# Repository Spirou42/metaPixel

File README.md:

# metaPixel
**A colourful open source art project.**

![Plasma Image][plasmaStripes]

## Description
metaPixel is a (mostly) 3D printed, modular, extendable, magnetic pixel display for showing "retro" animations well known from the *good old days*™.

![metaPixel Design][metaPixelAll]
The whole design uses a lot of magnets for adding strength to inter module connections, to hold the module cover and diffusors in place or to stick the modules onto the steel base.

The metaPixel display consists of 4 main parts:

1. steel plate
2. 20 metaPixel modules
3. controller and power supply 
4. Frame with connectors 

### Steel plate
The central structure of the whole installation is a 700 x 700 x 0.5 mm sheet of black painted steel. Both, the display modules as well as the controller and the power supply are attached with magnets to both sides of the plate.

### Frame
The steel plate is mounted to a wood frame with 20 ring magnets. 
![Frame][metaPixelFrame]

The wood frame contains cut outs for a standard power connector as well as for DMX (3 pin XLR) and USB connectors. 
![CutOuts][metaPixelFrameCutOuts]

### metaPixel Module
Each module contain 20 "intelligent" RGB LEDs in a 4 by 5 grid on a small printed carrier board.
![LED Stripes][ledStripes] 

The modules interconnect via a 3 pin connector. While the power connections goes straight from the input to the output with taps for each LED stripe. The data signal is routed on a zigzag path trough the stripes.
![metaPixel Box][metaPixelBox]

The LED carrier rests on top of four pillars which also contain some of the magnets.
![metaPixel Box with LEDs][metaPixelLedBox]

Four magnets in the corners of the box holds the cover and grid in place.
![metaPixelWholeBox][metaPixelWholeBox]

[plasmaStripes]: Resources/Color_lines.jpg "Plasma Stripes"
[ledStripes]: Resources/LEDs.png "LED-Base"
[metaPixelBox]: Resources/Box.png "megaPixel box with connectors"
[metaPixelLedBox]: Resources/LED_BOX.png "box with LED carrier"
[metaPixelFrame]: Resources/Frame.png "Frame with connectors and magnets"
[metaPixelFrameCutOuts]: Resources/FrameCutouts.png "Frame connectors"
[metaPixelAll]: Resources/metaPixelFull.png "metaPixel Display"
[metaPixelWholeBox]: Resources/metaPixel-Full.png "a full rendered metaPixel module"
[allParts]: Resources/Components.jpg "Photo of all parts of a metaPixel"

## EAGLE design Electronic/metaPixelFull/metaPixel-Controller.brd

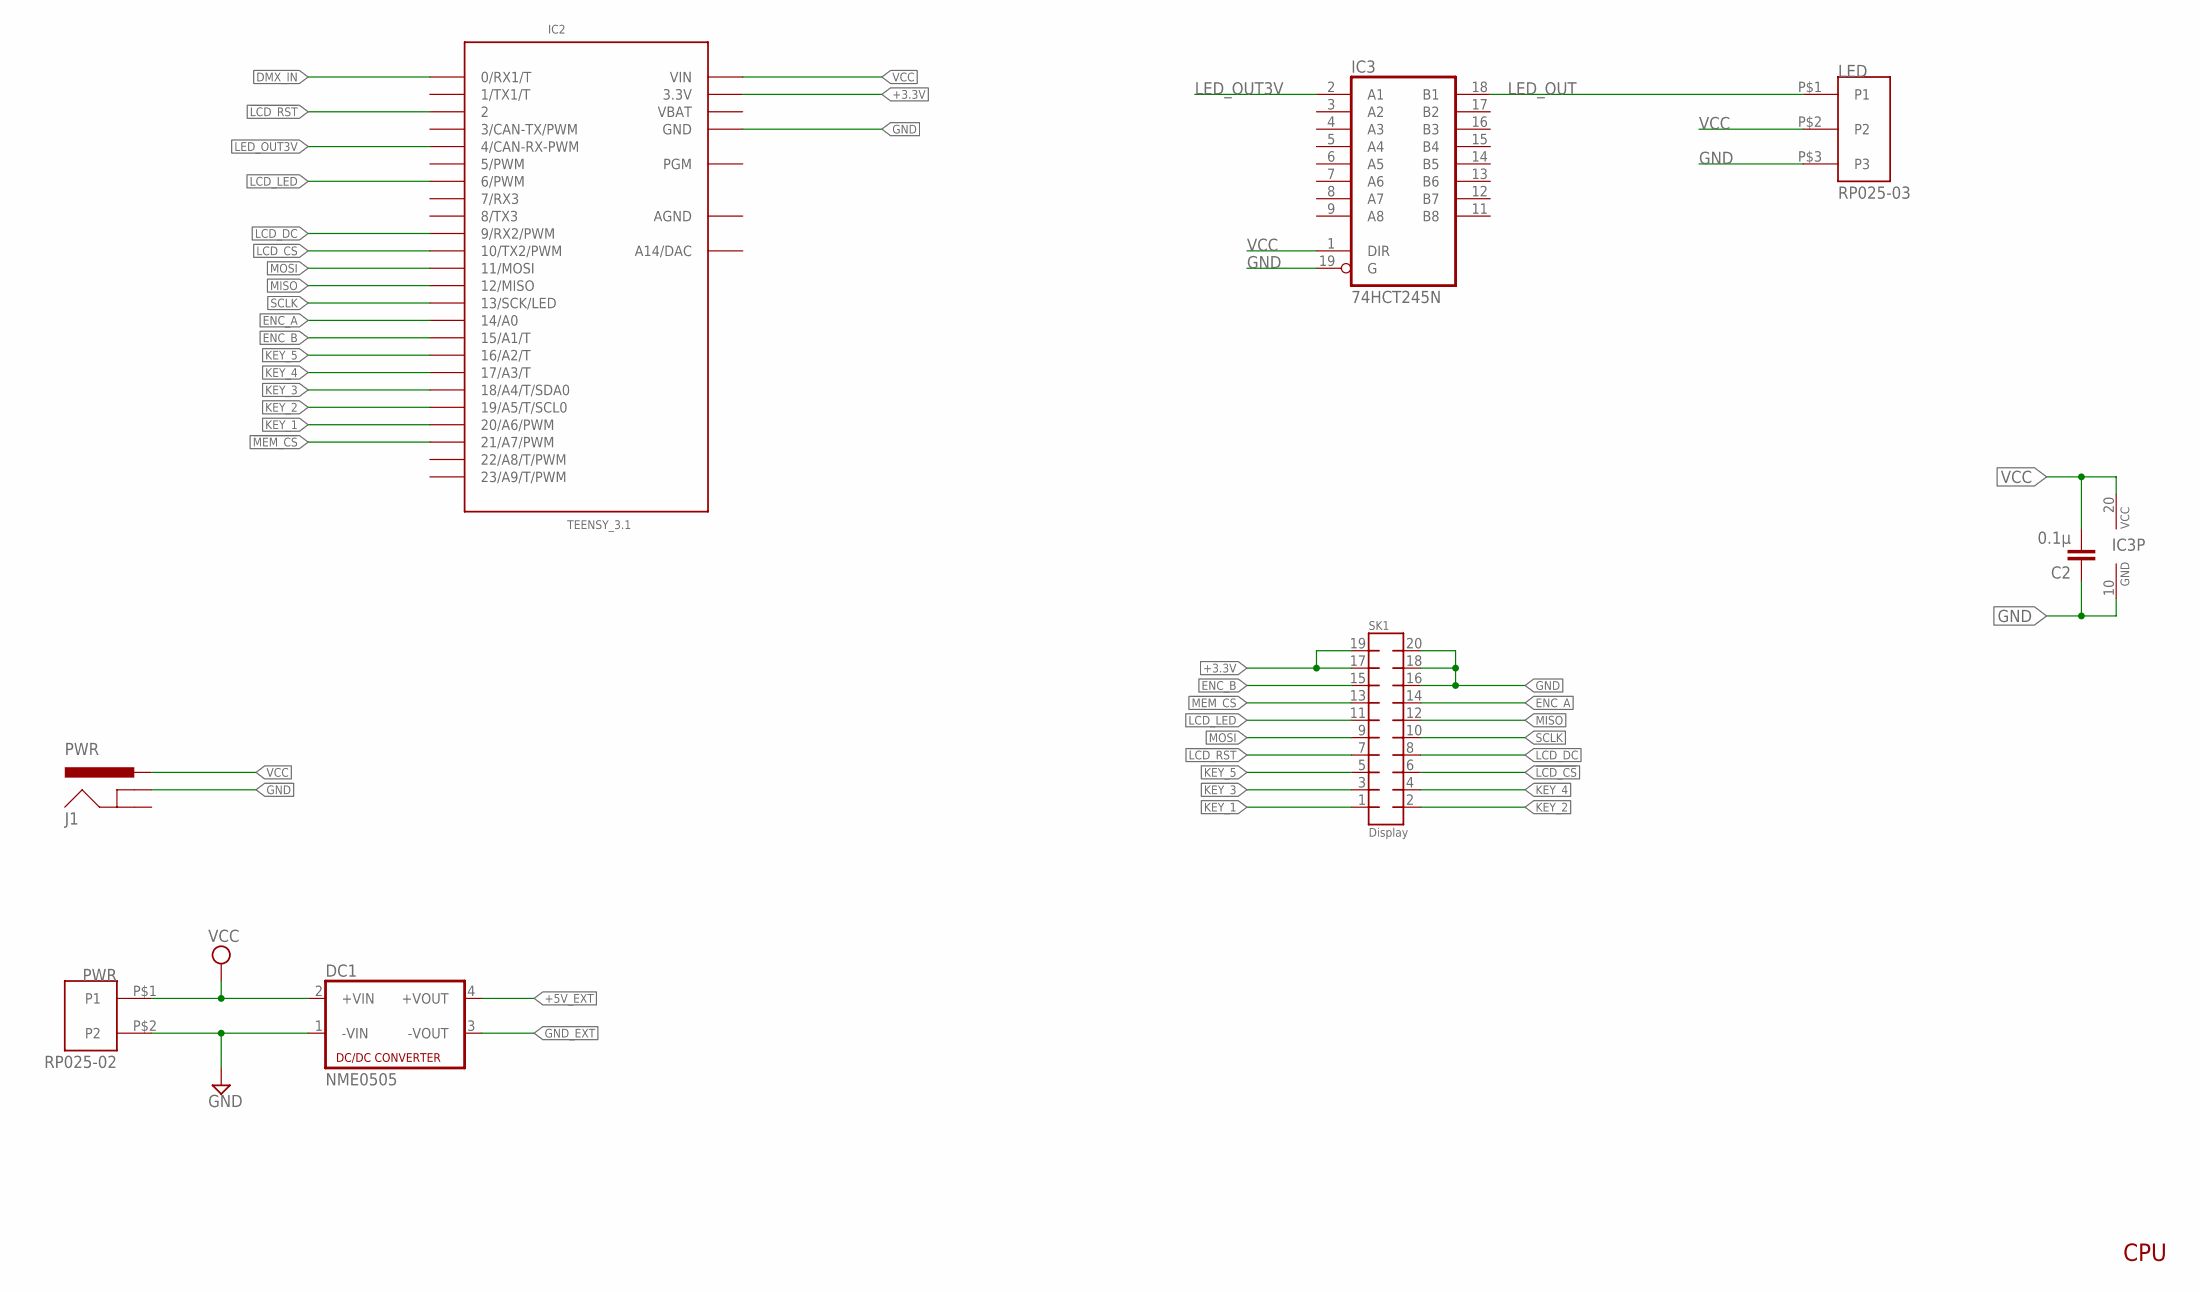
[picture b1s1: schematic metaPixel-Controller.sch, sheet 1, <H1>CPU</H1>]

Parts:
C2: 0.1µ; C025-030X050
DC1: NME0505; NME
IC2: TEENSY_3.1; TEENSY3-OUTER_ROW
IC3: 74HCT245N; DIL20
J1: PWR; POWER_JACK_SLOT
LED: RP025-03
PWR: RP025-02
SK1: Display; AMP-215079-20

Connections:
!LCD_CS: IC2.10 (10/TX2/PWM), SK1.6
!LCD_RST: IC2.2, SK1.7
!MEM_CS: IC2.21/A7 (21/A7/PWM), SK1.13
+3.3V: IC2.3.3V, IC2.3.3V1 (3.3V), SK1.17, SK1.19
+5V_EXT: DC1.4 (+VOUT); also elsewhere on the board
AGND: IC2.AGND
DMX_IN: IC2.0 (0/RX1/T); also elsewhere on the board
ENC_A: IC2.14/A0, SK1.14
ENC_B: IC2.15/A1 (15/A1/T), SK1.15
GND: C2.1, DC1.1 (-VIN), IC2.GND, IC2.GND1 (GND), IC3.10 (GND), IC3.19 (G), J1.GND@1 (GNDBREAK), LED.P$3 (P3), PWR.P$2 (P2), SK1.16, SK1.18, SK1.20; also elsewhere on the board
GND_EXT: DC1.3 (-VOUT); also elsewhere on the board
KEY_1: IC2.20/A6 (20/A6/PWM), SK1.1
KEY_2: IC2.19/A5 (19/A5/T/SCL0), SK1.2
KEY_3: IC2.18/A4 (18/A4/T/SDA0), SK1.3
KEY_4: IC2.17/A3 (17/A3/T), SK1.4
KEY_5: IC2.16/A2 (16/A2/T), SK1.5
LCD_DC: IC2.9 (9/RX2/PWM), SK1.8
LCD_LED: IC2.6 (6/PWM), SK1.11
LED_OUT: IC3.18 (B1), LED.P$1 (P1)
LED_OUT3V: IC2.4 (4/CAN-RX-PWM), IC3.2 (A1)
MISO: IC2.12 (12/MISO), SK1.12
MOSI: IC2.11 (11/MOSI), SK1.9
SCLK: IC2.13 (13/SCK/LED), SK1.10
VBAT: IC2.VBAT
VCC: C2.2, DC1.2 (+VIN), IC2.VIN, IC3.1 (DIR), IC3.20 (VCC), J1.PWR, LED.P$2 (P2), PWR.P$1 (P1); also elsewhere on the board

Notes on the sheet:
CPU

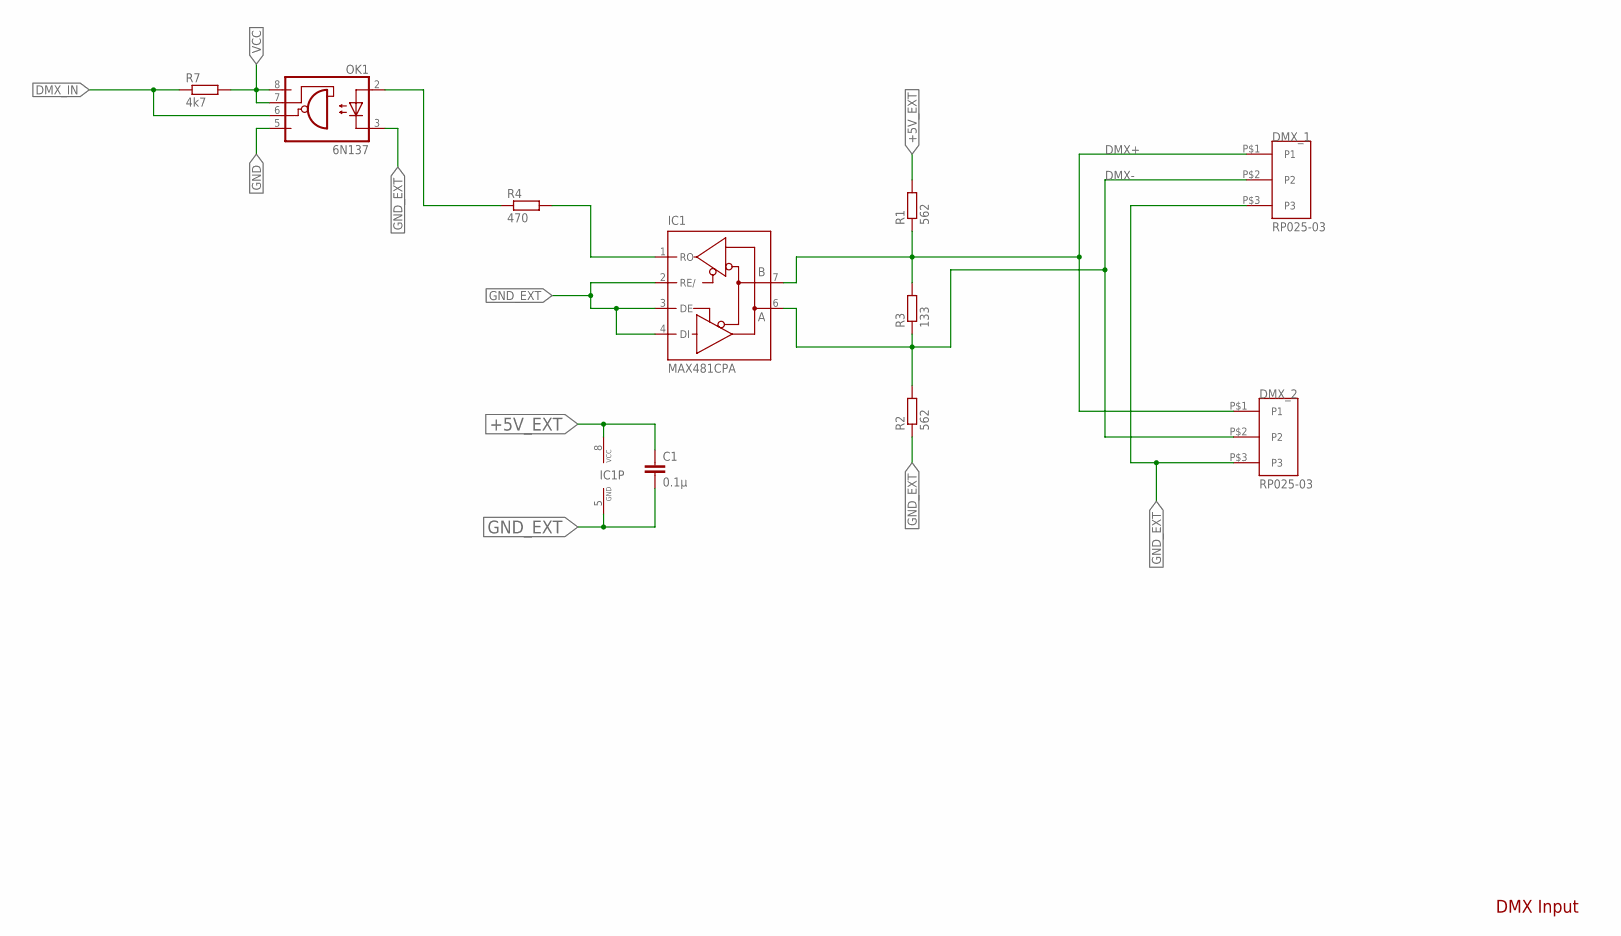
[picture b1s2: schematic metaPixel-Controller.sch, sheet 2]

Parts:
C1: 0.1µ; C025-030X050
DMX_1, DMX_2: RP025-03
IC1: MAX481CPA; DIL08
OK1: 6N137; DIL08
R1, R2: 562; 0207/7
R3: 133; 0207/7
R4: 470; 0207/10
R7: 4k7; 0207/10

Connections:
+5V_EXT: C1.1, IC1.8 (VCC), R1.2; also elsewhere on the board
DMX+: DMX_1.P$1 (P1), DMX_2.P$1 (P1), IC1.7 (B), R1.1, R3.2
DMX-: DMX_1.P$2 (P2), DMX_2.P$2 (P2), IC1.6 (A), R2.2, R3.1
DMX_IN: OK1.6 (VO), R7.1; also elsewhere on the board
GND: OK1.5 (GND); also elsewhere on the board
GND_EXT: C1.2, DMX_1.P$3 (P3), DMX_2.P$3 (P3), IC1.2 (RE/), IC1.3 (DE), IC1.4 (DI), IC1.5 (GND), OK1.3 (C), R2.1; also elsewhere on the board
unnamed: OK1.2 (A), R4.1
unnamed: IC1.1 (RO), R4.2
VCC: OK1.7 (VE), OK1.8 (VCC), R7.2; also elsewhere on the board

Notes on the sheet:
DMX Input

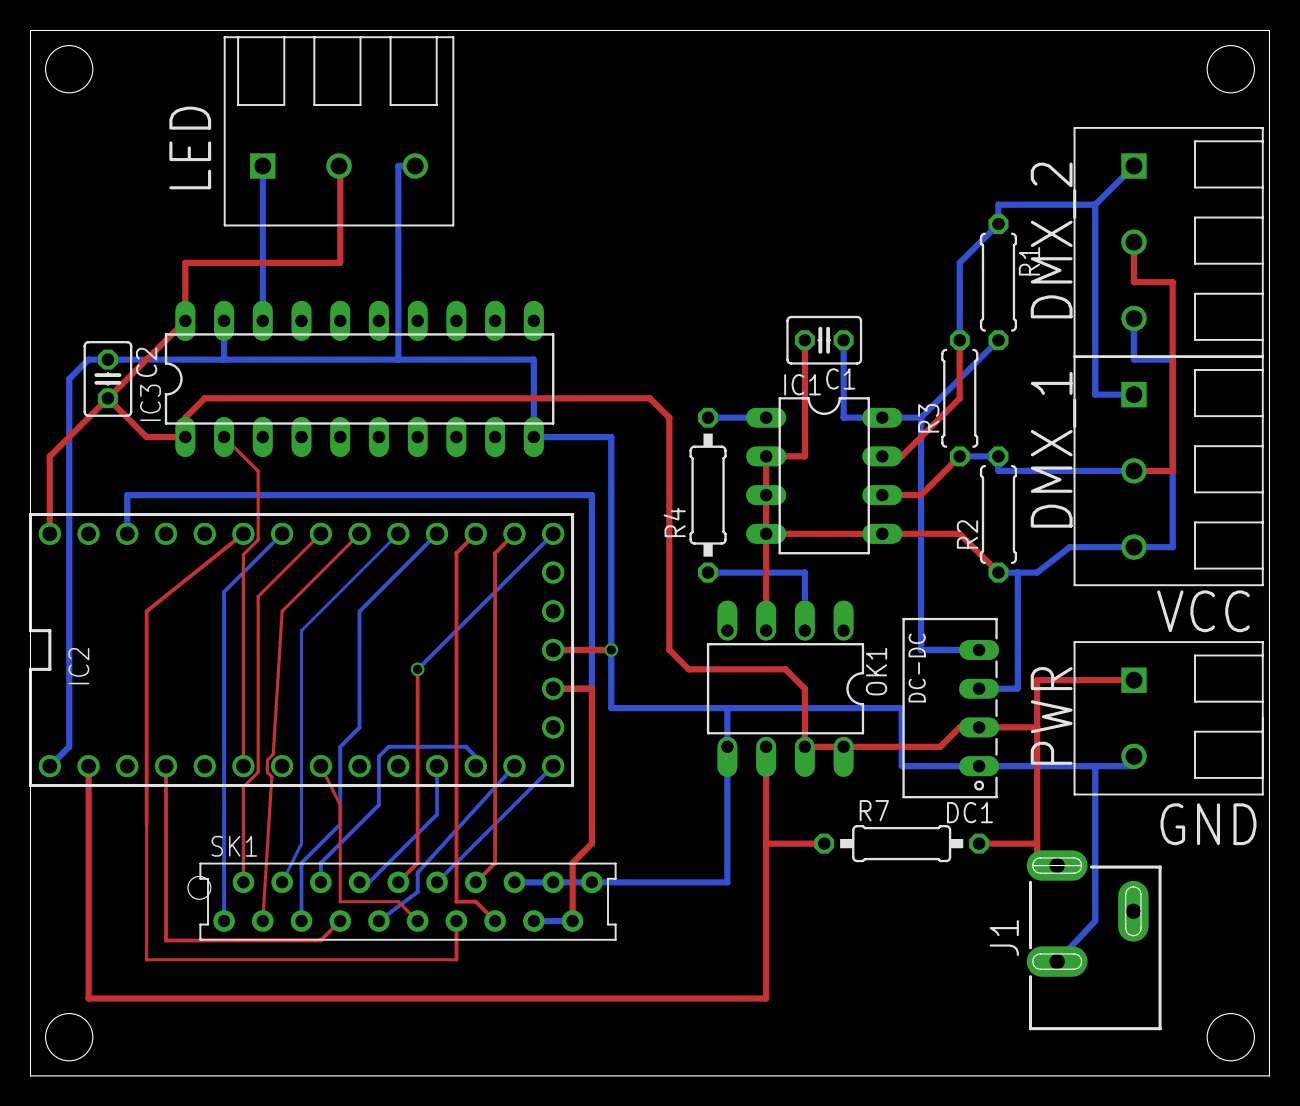
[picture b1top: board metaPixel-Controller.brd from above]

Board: 2 copper layers, 81.3 x 68.6 mm, 18 parts (0 on the bottom side), 27 nets.

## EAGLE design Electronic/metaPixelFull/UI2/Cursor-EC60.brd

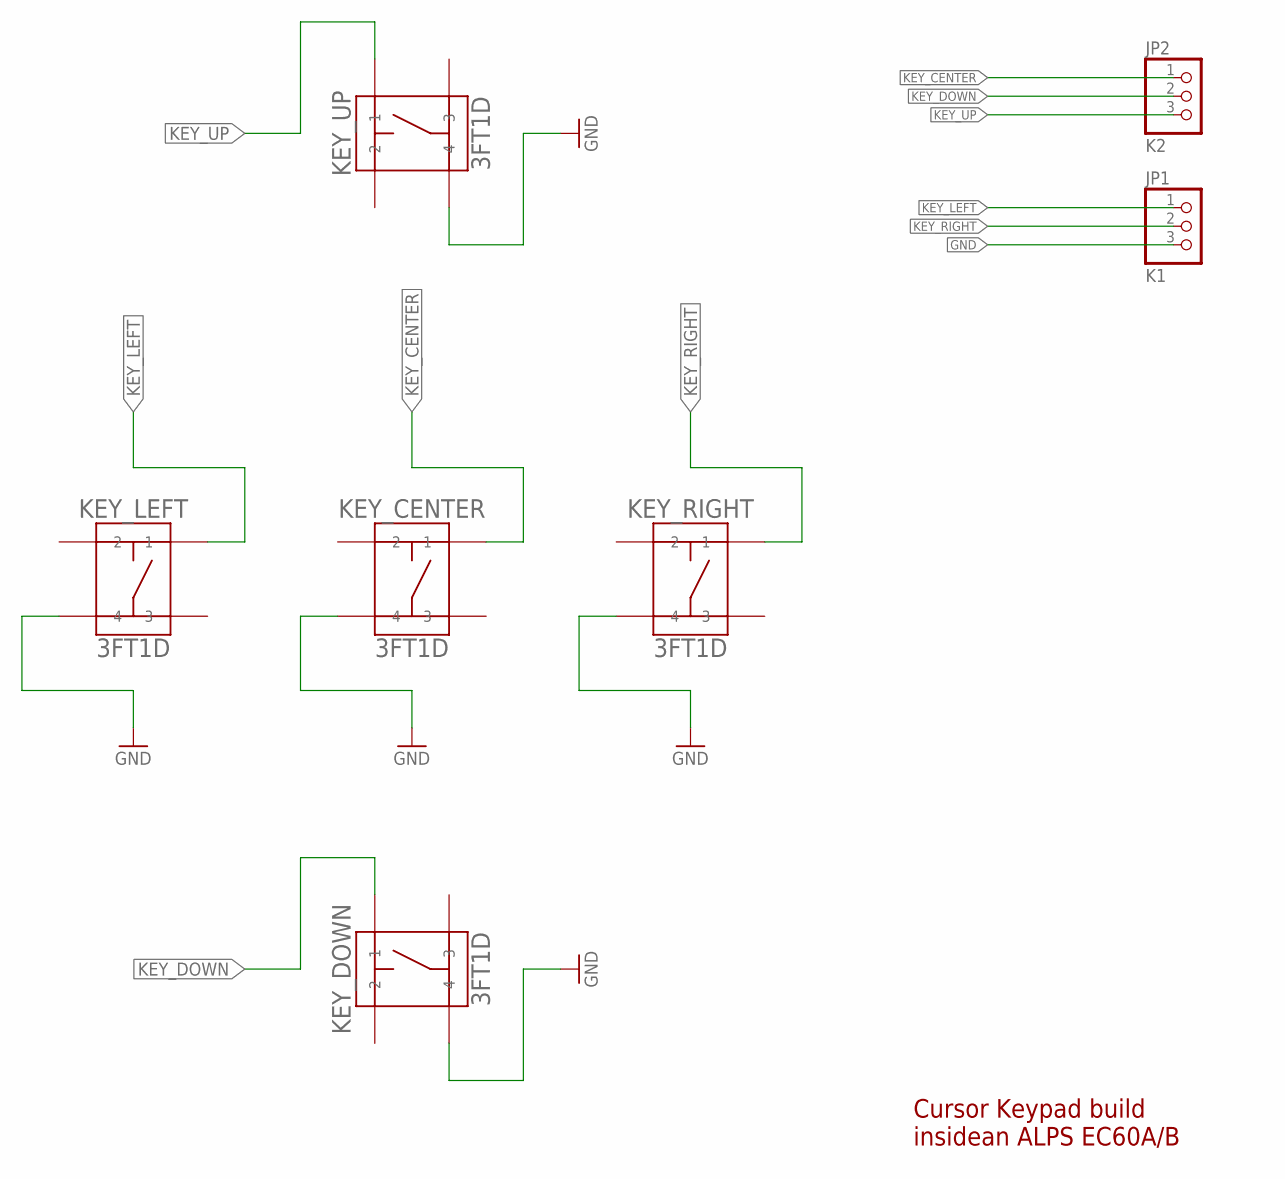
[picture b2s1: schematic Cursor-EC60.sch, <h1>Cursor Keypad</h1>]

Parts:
JP1: K1; 1X03
JP2: K2; 1X03
KEY_CENTER: 3FT1D; 3FT
KEY_DOWN: 3FT1D; 3FT
KEY_LEFT: 3FT1D; 3FT
KEY_RIGHT: 3FT1D; 3FT
KEY_UP: 3FT1D; 3FT

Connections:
GND: JP1.3, KEY_CENTER.P$4 (4), KEY_DOWN.P$4 (4), KEY_LEFT.P$4 (4), KEY_RIGHT.P$4 (4), KEY_UP.P$4 (4)
KEY_CENTER: JP2.1, KEY_CENTER.P$1 (1)
KEY_DOWN: JP2.2, KEY_DOWN.P$1 (1)
KEY_LEFT: JP1.1, KEY_LEFT.P$1 (1)
KEY_RIGHT: JP1.2, KEY_RIGHT.P$1 (1)
KEY_UP: JP2.3, KEY_UP.P$1 (1)

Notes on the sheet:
Cursor Keypad build insidean ALPS EC60A/B

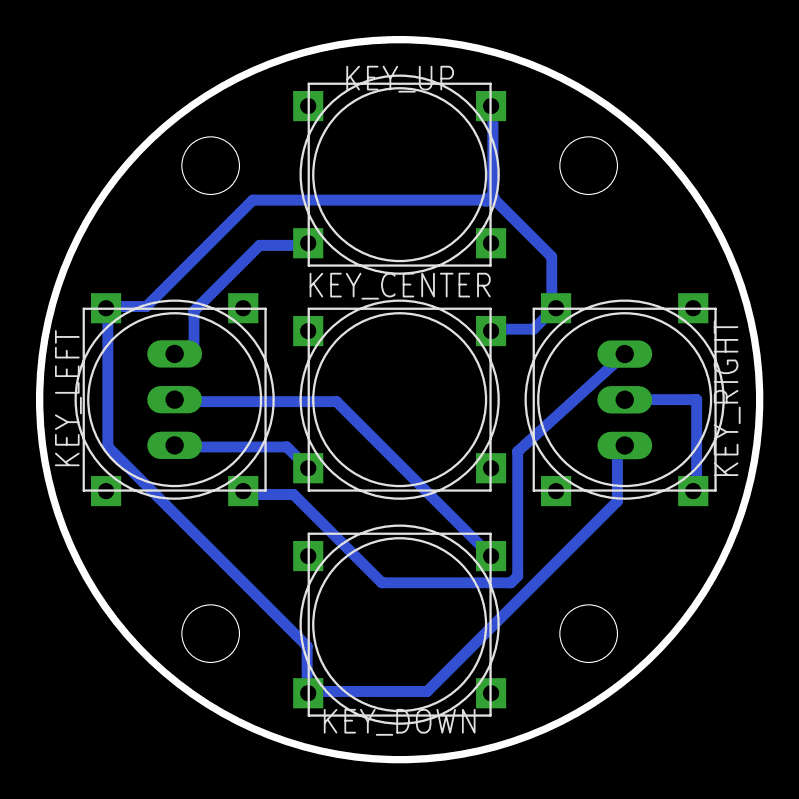
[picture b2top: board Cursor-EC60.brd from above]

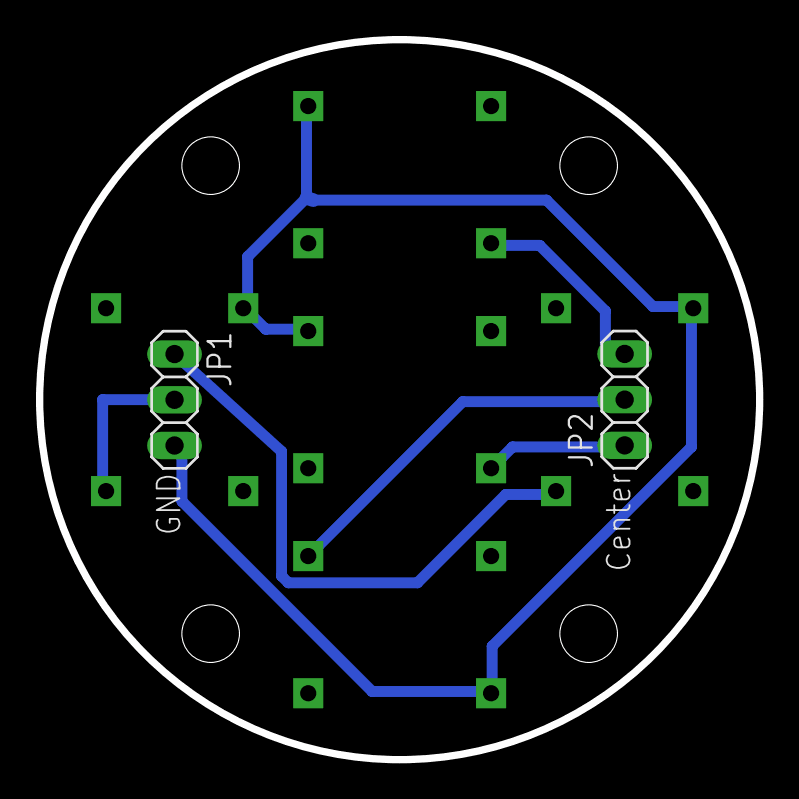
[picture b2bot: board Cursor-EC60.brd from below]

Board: 2 copper layers, 40.0 x 40.0 mm, 7 parts (2 on the bottom side), 6 nets.

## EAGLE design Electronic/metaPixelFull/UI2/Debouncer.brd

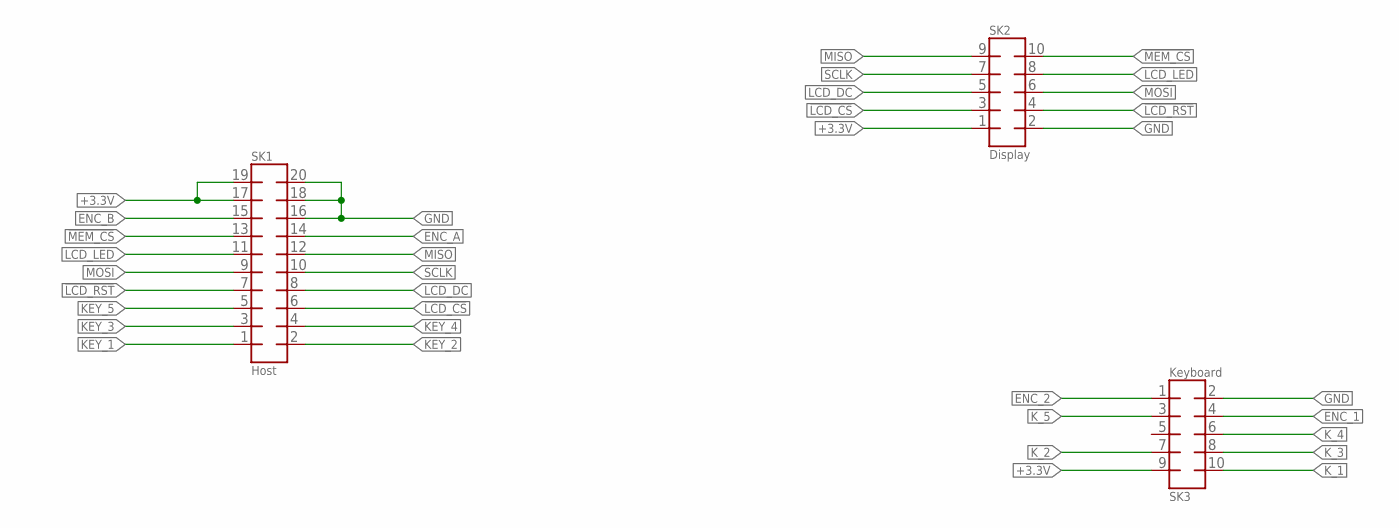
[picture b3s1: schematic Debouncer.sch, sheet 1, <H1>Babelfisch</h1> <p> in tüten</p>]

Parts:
SK1: Host; AMP-215079-20
SK2: Display; AMP-215079-10
SK3: Keyboard; AMP-215079-10

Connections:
!LCD_CS: SK1.6, SK2.3
!LCD_RST: SK1.7, SK2.4
!MEM_CS: SK1.13, SK2.10
+3.3V: SK1.17, SK1.19, SK2.1, SK3.9; also elsewhere on the board
ENC_1: SK3.4; also elsewhere on the board
ENC_2: SK3.1; also elsewhere on the board
ENC_A: SK1.14; also elsewhere on the board
ENC_B: SK1.15; also elsewhere on the board
GND: SK1.16, SK1.18, SK1.20, SK2.2, SK3.2; also elsewhere on the board
KEY_1: SK1.1; also elsewhere on the board
KEY_2: SK1.2; also elsewhere on the board
KEY_3: SK1.3; also elsewhere on the board
KEY_4: SK1.4; also elsewhere on the board
KEY_5: SK1.5; also elsewhere on the board
K_1: SK3.10; also elsewhere on the board
K_2: SK3.7; also elsewhere on the board
K_3: SK3.8; also elsewhere on the board
K_4: SK3.6; also elsewhere on the board
K_5: SK3.3; also elsewhere on the board
LCD_DC: SK1.8, SK2.5
LCD_LED: SK1.11, SK2.8
MISO: SK1.12, SK2.9
MOSI: SK1.9, SK2.6
SCLK: SK1.10, SK2.7

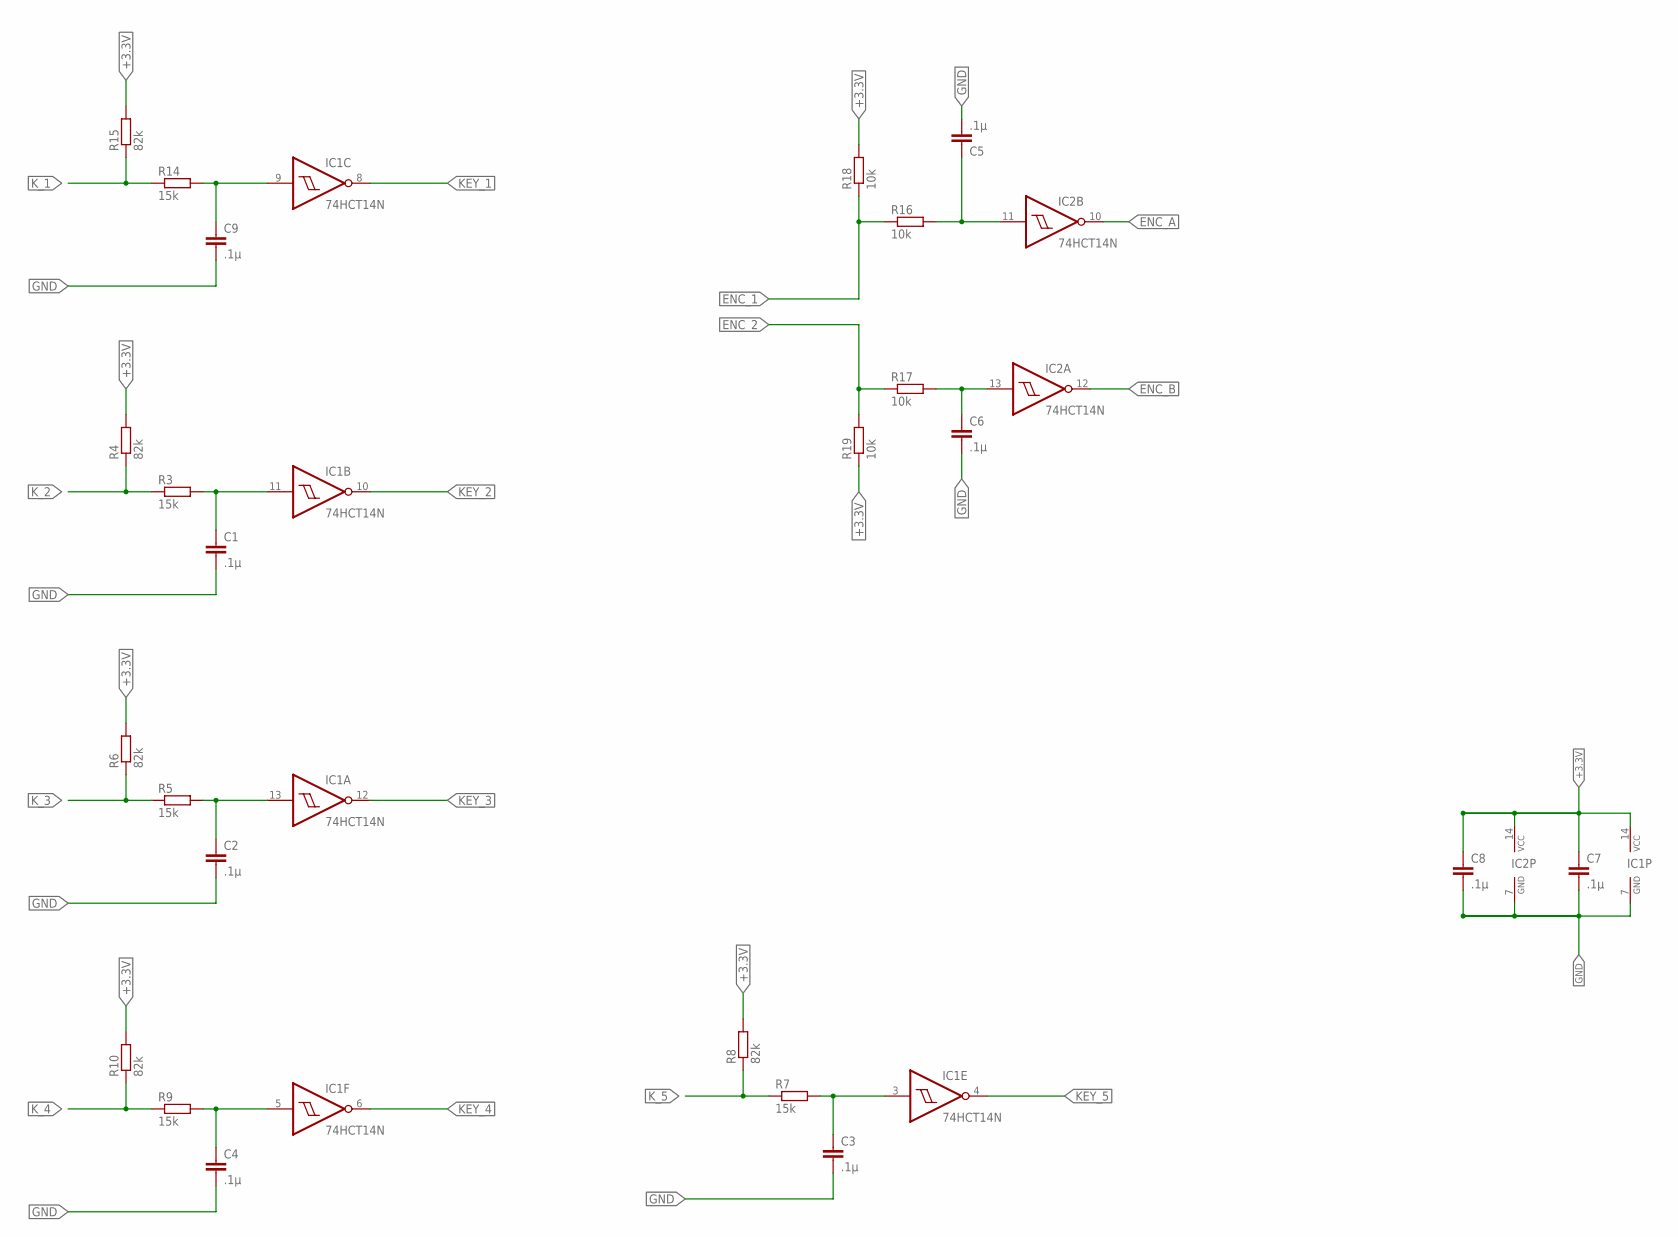
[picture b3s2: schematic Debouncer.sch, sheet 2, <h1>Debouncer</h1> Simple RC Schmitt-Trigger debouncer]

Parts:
C1, C2, C3, C4, C5, C6, C7, C8, C9: .1µ; C025-024X044
IC1, IC2: 74HCT14N; DIL14
R3, R5, R7, R9, R14: 15k; 0204/7
R4, R6, R8, R10, R15: 82k; 0204/7
R16, R17, R18, R19: 10k; 0204/7

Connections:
+3.3V: C7.1, C8.1, IC1.14 (VCC), IC2.14 (VCC), R4.2, R6.2, R8.2, R10.2, R15.2, R18.2, R19.1; also elsewhere on the board
ENC1: C5.1, IC2.11 (I), R16.2
ENC2: C6.1, IC2.13 (I), R17.2
ENC_1: R16.1, R18.1; also elsewhere on the board
ENC_2: R17.1, R19.2; also elsewhere on the board
ENC_A: IC2.10 (O); also elsewhere on the board
ENC_B: IC2.12 (O); also elsewhere on the board
GND: C1.2, C2.2, C3.2, C4.2, C5.2, C6.2, C7.2, C8.2, C9.2, IC1.7 (GND), IC2.7 (GND); also elsewhere on the board
K1: C9.1, IC1.9 (I), R14.2
K2: C1.1, IC1.11 (I), R3.2
K3: C2.1, IC1.13 (I), R5.2
K4: C3.1, IC1.3 (I), R7.2
K5: C4.1, IC1.5 (I), R9.2
KEY_1: IC1.8 (O); also elsewhere on the board
KEY_2: IC1.10 (O); also elsewhere on the board
KEY_3: IC1.12 (O); also elsewhere on the board
KEY_4: IC1.6 (O); also elsewhere on the board
KEY_5: IC1.4 (O); also elsewhere on the board
K_1: R14.1, R15.1; also elsewhere on the board
K_2: R3.1, R4.1; also elsewhere on the board
K_3: R5.1, R6.1; also elsewhere on the board
K_4: R9.1, R10.1; also elsewhere on the board
K_5: R7.1, R8.1; also elsewhere on the board

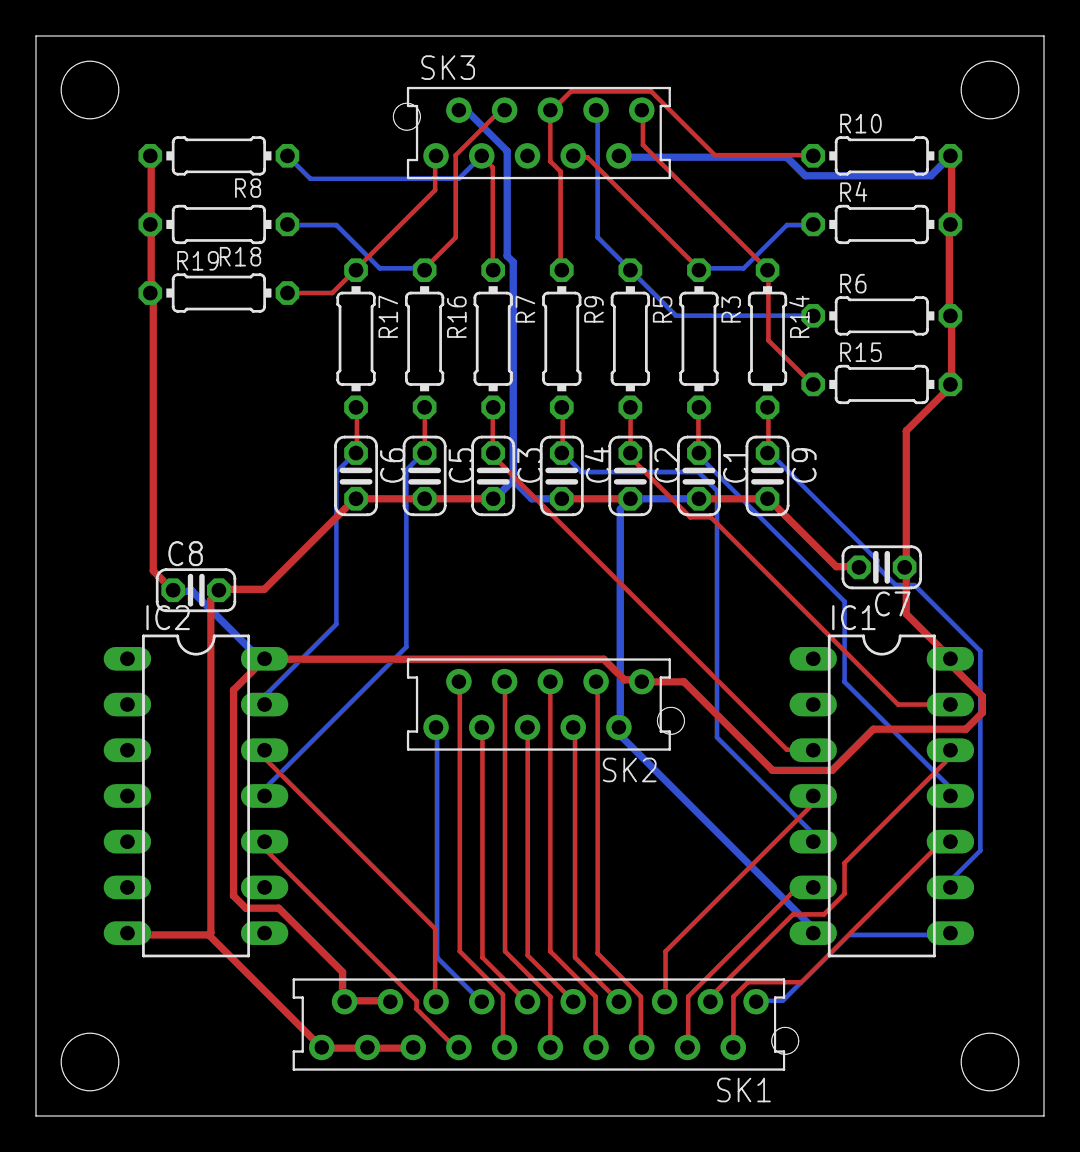
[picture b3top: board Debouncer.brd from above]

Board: 2 copper layers, 56.0 x 60.0 mm, 28 parts (0 on the bottom side), 31 nets.

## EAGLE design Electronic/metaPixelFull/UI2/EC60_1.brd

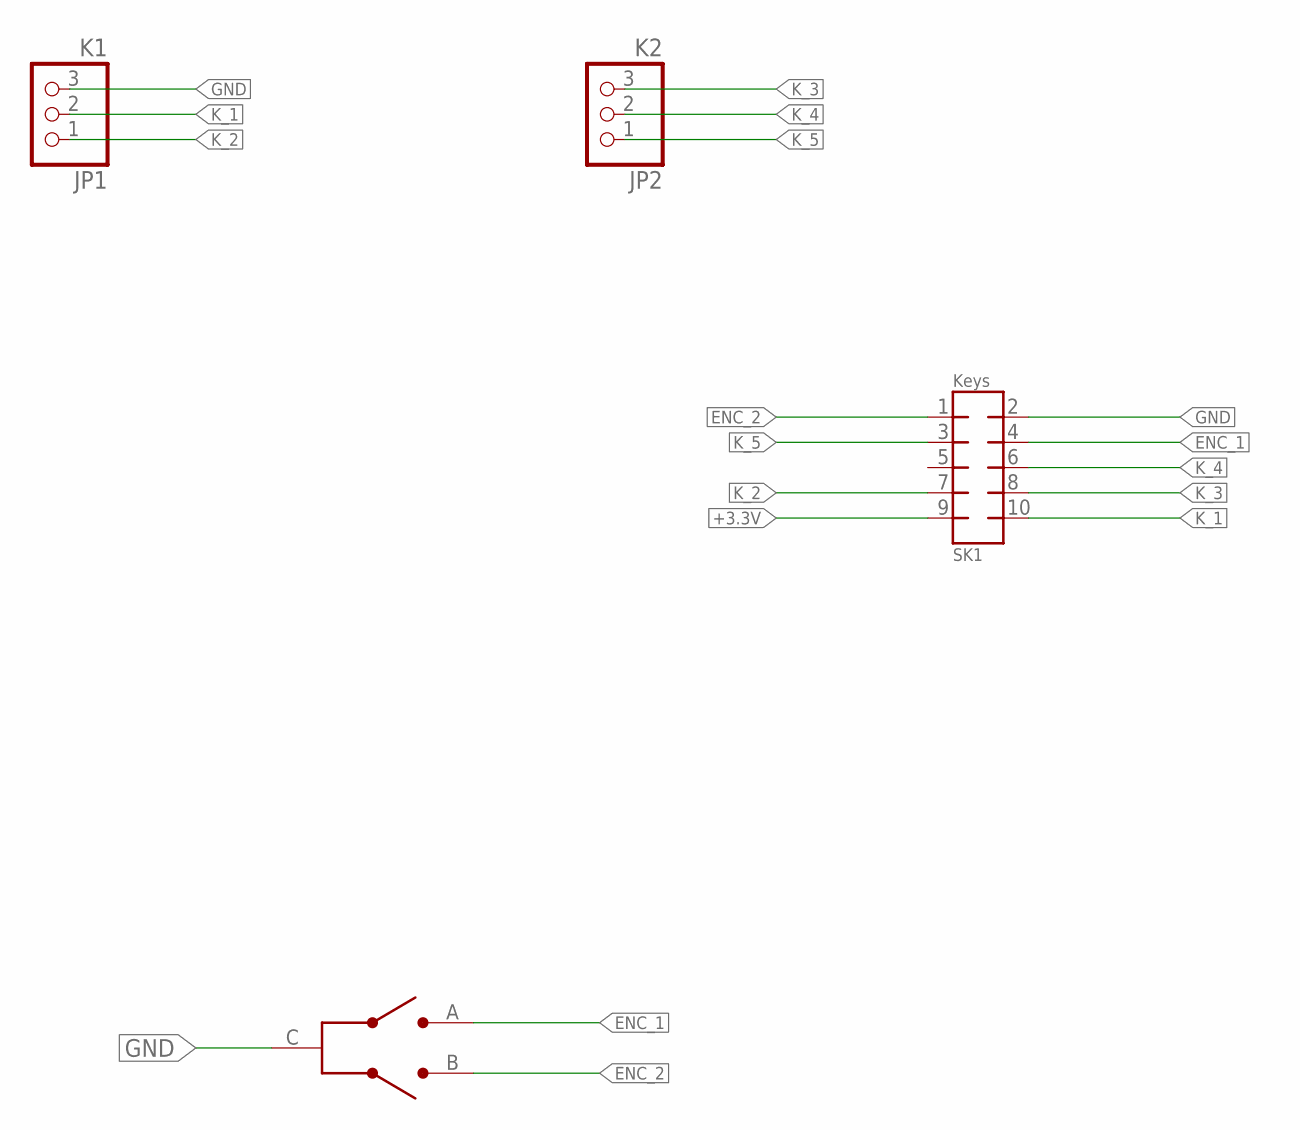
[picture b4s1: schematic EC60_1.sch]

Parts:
JP1: K1; 1X03
JP2: K2; 1X03
SK1: Keys; AMP-215079-10
U$1: EC60A

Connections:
+3.3V: SK1.9
ENC_1: SK1.4, U$1.A
ENC_2: SK1.1, U$1.B
GND: JP1.3, SK1.2, U$1.C
K_1: JP1.2, SK1.10
K_2: JP1.1, SK1.7
K_3: JP2.3, SK1.8
K_4: JP2.2, SK1.6
K_5: JP2.1, SK1.3

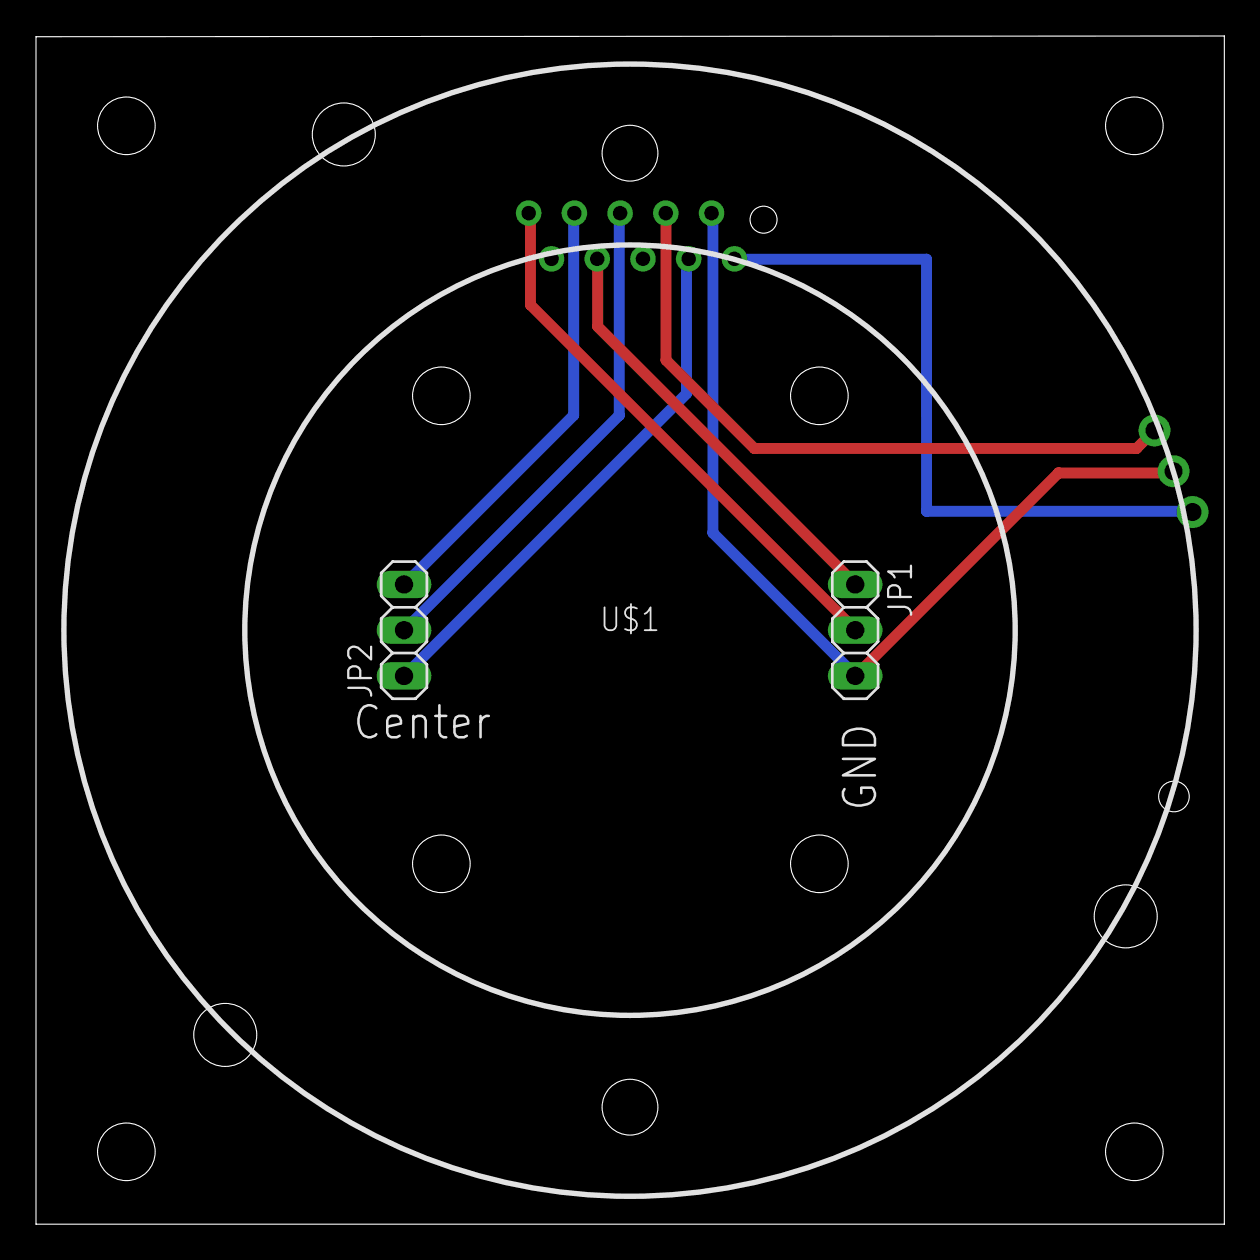
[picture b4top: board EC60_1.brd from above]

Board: 2 copper layers, 66.0 x 66.0 mm, 4 parts (1 on the bottom side), 8 nets.

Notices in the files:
parts and their libraries:
SparkFun-Connectors: Licensing: CC v3.0 Share-Alike You are welcome to use this library for commercial purposes.
